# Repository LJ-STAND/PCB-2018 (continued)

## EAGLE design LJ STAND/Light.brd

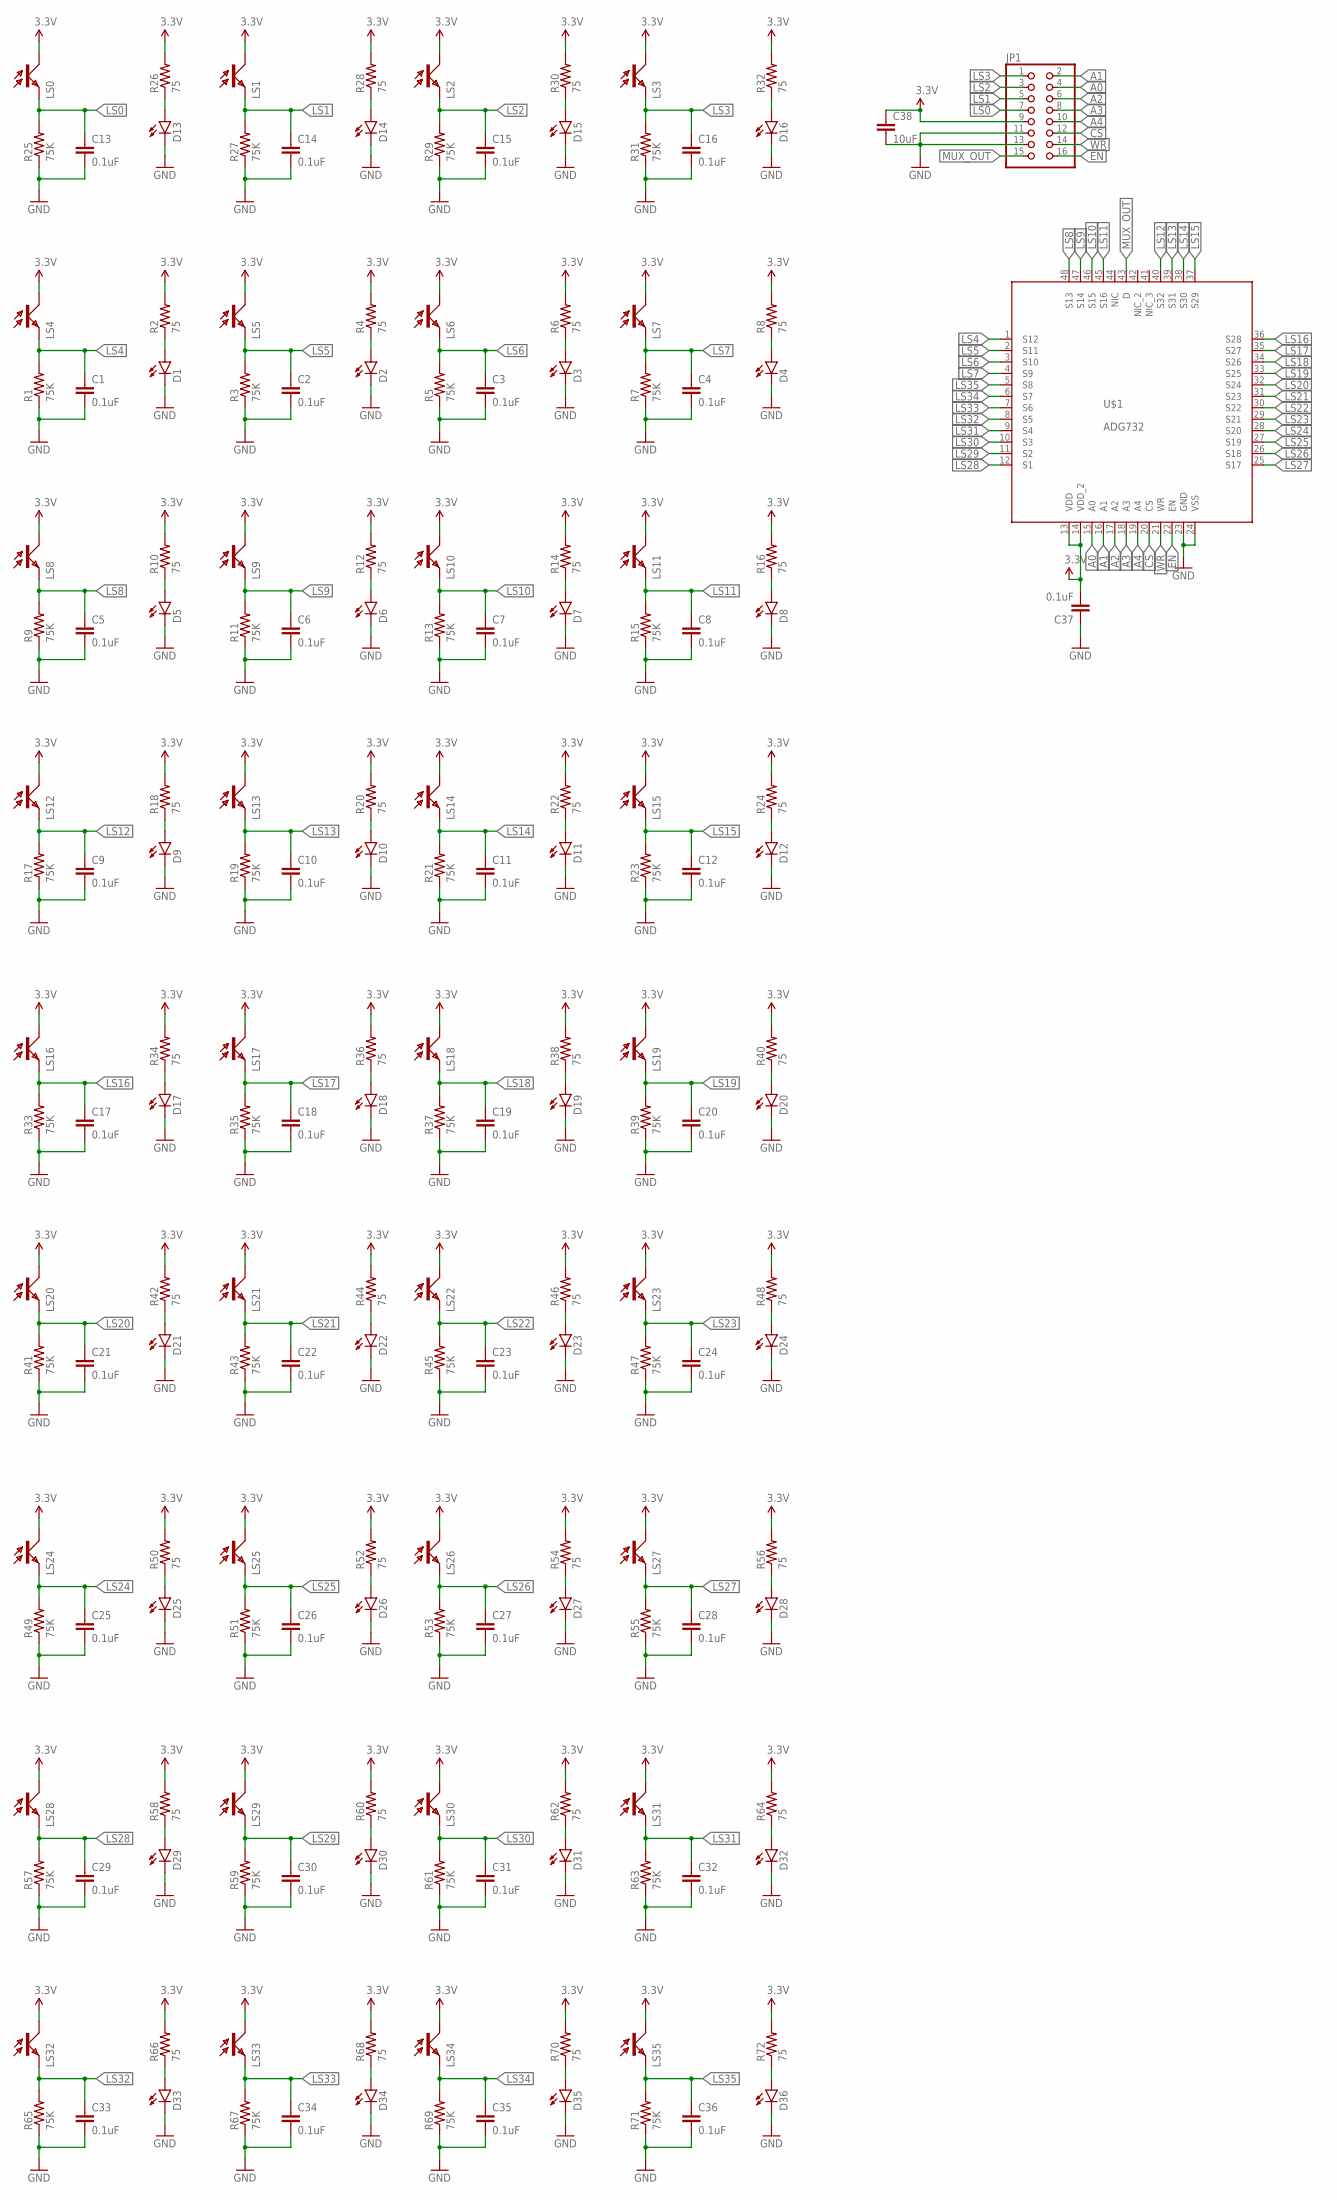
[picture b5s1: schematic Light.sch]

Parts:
C1, C2, C3, C4, C5, C6, C7, C8, C9, C10, C11, C12, C13, C14, C15, C16, C17, C18, C19, C20, C21, C22, C23, C24, C25, C26, C27, C28, C29, C30, C31, C32, C33, C34, C35, C36, C37: 0.1uF; 0603-CAP
C38: 10uF; 0805
D1, D2, D3, D4, D5, D6, D7, D8, D9, D10, D11, D12, D13, D14, D15, D16, D17, D18, D19, D20, D21, D22, D23, D24, D25, D26, D27, D28, D29, D30, D31, D32, D33, D34, D35, D36: LED0603; LED-0603
JP1: PINHD-2X8SMT; 2X08_SMT
LS0, LS1, LS2, LS3, LS4, LS5, LS6, LS7, LS8, LS9, LS10, LS11, LS12, LS13, LS14, LS15, LS16, LS17, LS18, LS19, LS20, LS21, LS22, LS23, LS24, LS25, LS26, LS27, LS28, LS29, LS30, LS31, LS32, LS33, LS34, LS35: ALS; SMD
R1, R3, R5, R7, R9, R11, R13, R15, R17, R19, R21, R23, R25, R27, R29, R31, R33, R35, R37, R39, R41, R43, R45, R47, R49, R51, R53, R55, R57, R59, R61, R63, R65, R67, R69, R71: 75K; 0603-RES
R2, R4, R6, R8, R10, R12, R14, R16, R18, R20, R22, R24, R26, R28, R30, R32, R34, R36, R38, R40, R42, R44, R46, R48, R50, R52, R54, R56, R58, R60, R62, R64, R66, R68, R70, R72: 75; 0603-RES
U$1: ADG732; QFP-7X7-48-NO-EXP

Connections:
3.3V: C37.2, C38.1, JP1.9, LS0.C, LS1.C, LS2.C, LS3.C, LS4.C, LS5.C, LS6.C, LS7.C, LS8.C, LS9.C, LS10.C, LS11.C, LS12.C, LS13.C, LS14.C, LS15.C, LS16.C, LS17.C, LS18.C, LS19.C, LS20.C, LS21.C, LS22.C, LS23.C, LS24.C, LS25.C, LS26.C, LS27.C, LS28.C, LS29.C, LS30.C, LS31.C, LS32.C, LS33.C, LS34.C, LS35.C, R2.2, R4.2, R6.2, R8.2, R10.2, R12.2, R14.2, R16.2, R18.2, R20.2, R22.2, R24.2, R26.2, R28.2, R30.2, R32.2, R34.2, R36.2, R38.2, R40.2, R42.2, R44.2, R46.2, R48.2, R50.2, R52.2, R54.2, R56.2, R58.2, R60.2, R62.2, R64.2, R66.2, R68.2, R70.2, R72.2, U$1.13 (VDD), U$1.14 (VDD_2)
A0: JP1.4, U$1.15 (A0)
A1: JP1.2, U$1.16 (A1)
A2: JP1.6, U$1.17 (A2)
A3: JP1.8, U$1.18 (A3)
A4: JP1.10, U$1.19 (A4)
CS: JP1.12, U$1.20 (CS)
EN: JP1.16, U$1.22 (EN)
GND: C1.2, C2.2, C3.2, C4.2, C5.2, C6.2, C7.2, C8.2, C9.2, C10.2, C11.2, C12.2, C13.2, C14.2, C15.2, C16.2, C17.2, C18.2, C19.2, C20.2, C21.2, C22.2, C23.2, C24.2, C25.2, C26.2, C27.2, C28.2, C29.2, C30.2, C31.2, C32.2, C33.2, C34.2, C35.2, C36.2, C37.1, C38.2, D1.C, D2.C, D3.C, D4.C, D5.C, D6.C, D7.C, D8.C, D9.C, D10.C, D11.C, D12.C, D13.C, D14.C, D15.C, D16.C, D17.C, D18.C, D19.C, D20.C, D21.C, D22.C, D23.C, D24.C, D25.C, D26.C, D27.C, D28.C, D29.C, D30.C, D31.C, D32.C, D33.C, D34.C, D35.C, D36.C, JP1.11, JP1.13, R1.1, R3.1, R5.1, R7.1, R9.1, R11.1, R13.1, R15.1, R17.1, R19.1, R21.1, R23.1, R25.1, R27.1, R29.1, R31.1, R33.1, R35.1, R37.1, R39.1, R41.1, R43.1, R45.1, R47.1, R49.1, R51.1, R53.1, R55.1, R57.1, R59.1, R61.1, R63.1, R65.1, R67.1, R69.1, R71.1, U$1.23 (GND), U$1.24 (VSS)
LS0: C13.1, JP1.7, LS0.E, R25.2
LS1: C14.1, JP1.5, LS1.E, R27.2
LS2: C15.1, JP1.3, LS2.E, R29.2
LS3: C16.1, JP1.1, LS3.E, R31.2
LS4: C1.1, LS4.E, R1.2, U$1.1 (S12)
LS5: C2.1, LS5.E, R3.2, U$1.2 (S11)
LS6: C3.1, LS6.E, R5.2, U$1.3 (S10)
LS7: C4.1, LS7.E, R7.2, U$1.4 (S9)
LS8: C5.1, LS8.E, R9.2, U$1.48 (S13)
LS9: C6.1, LS9.E, R11.2, U$1.47 (S14)
LS10: C7.1, LS10.E, R13.2, U$1.46 (S15)
LS11: C8.1, LS11.E, R15.2, U$1.45 (S16)
LS12: C9.1, LS12.E, R17.2, U$1.40 (S32)
LS13: C10.1, LS13.E, R19.2, U$1.39 (S31)
LS14: C11.1, LS14.E, R21.2, U$1.38 (S30)
LS15: C12.1, LS15.E, R23.2, U$1.37 (S29)
LS16: C17.1, LS16.E, R33.2, U$1.36 (S28)
LS17: C18.1, LS17.E, R35.2, U$1.35 (S27)
LS18: C19.1, LS18.E, R37.2, U$1.34 (S26)
LS19: C20.1, LS19.E, R39.2, U$1.33 (S25)
LS20: C21.1, LS20.E, R41.2, U$1.32 (S24)
LS21: C22.1, LS21.E, R43.2, U$1.31 (S23)
LS22: C23.1, LS22.E, R45.2, U$1.30 (S22)
LS23: C24.1, LS23.E, R47.2, U$1.29 (S21)
LS24: C25.1, LS24.E, R49.2, U$1.28 (S20)
LS25: C26.1, LS25.E, R51.2, U$1.27 (S19)
LS26: C27.1, LS26.E, R53.2, U$1.26 (S18)
LS27: C28.1, LS27.E, R55.2, U$1.25 (S17)
LS28: C29.1, LS28.E, R57.2, U$1.12 (S1)
LS29: C30.1, LS29.E, R59.2, U$1.11 (S2)
LS30: C31.1, LS30.E, R61.2, U$1.10 (S3)
LS31: C32.1, LS31.E, R63.2, U$1.9 (S4)
LS32: C33.1, LS32.E, R65.2, U$1.8 (S5)
LS33: C34.1, LS33.E, R67.2, U$1.7 (S6)
LS34: C35.1, LS34.E, R69.2, U$1.6 (S7)
LS35: C36.1, LS35.E, R71.2, U$1.5 (S8)
MUX_OUT: JP1.15, U$1.43 (D)
unnamed: D2.A, R4.1
unnamed: D1.A, R2.1
unnamed: D3.A, R6.1
unnamed: D4.A, R8.1
unnamed: D5.A, R10.1
unnamed: D6.A, R12.1
unnamed: D7.A, R14.1
unnamed: D8.A, R16.1
unnamed: D9.A, R18.1
unnamed: D10.A, R20.1
unnamed: D11.A, R22.1
unnamed: D12.A, R24.1
unnamed: D13.A, R26.1
unnamed: D14.A, R28.1
unnamed: D15.A, R30.1
unnamed: D16.A, R32.1
unnamed: D17.A, R34.1
unnamed: D18.A, R36.1
unnamed: D19.A, R38.1
unnamed: D20.A, R40.1
unnamed: D21.A, R42.1
unnamed: D22.A, R44.1
unnamed: D23.A, R46.1
unnamed: D24.A, R48.1
unnamed: D25.A, R50.1
unnamed: D26.A, R52.1
unnamed: D27.A, R54.1
unnamed: D28.A, R56.1
unnamed: D29.A, R58.1
unnamed: D30.A, R60.1
unnamed: D31.A, R62.1
unnamed: D32.A, R64.1
unnamed: D33.A, R66.1
unnamed: D34.A, R68.1
unnamed: D35.A, R70.1
unnamed: D36.A, R72.1
WR: JP1.14, U$1.21 (WR)

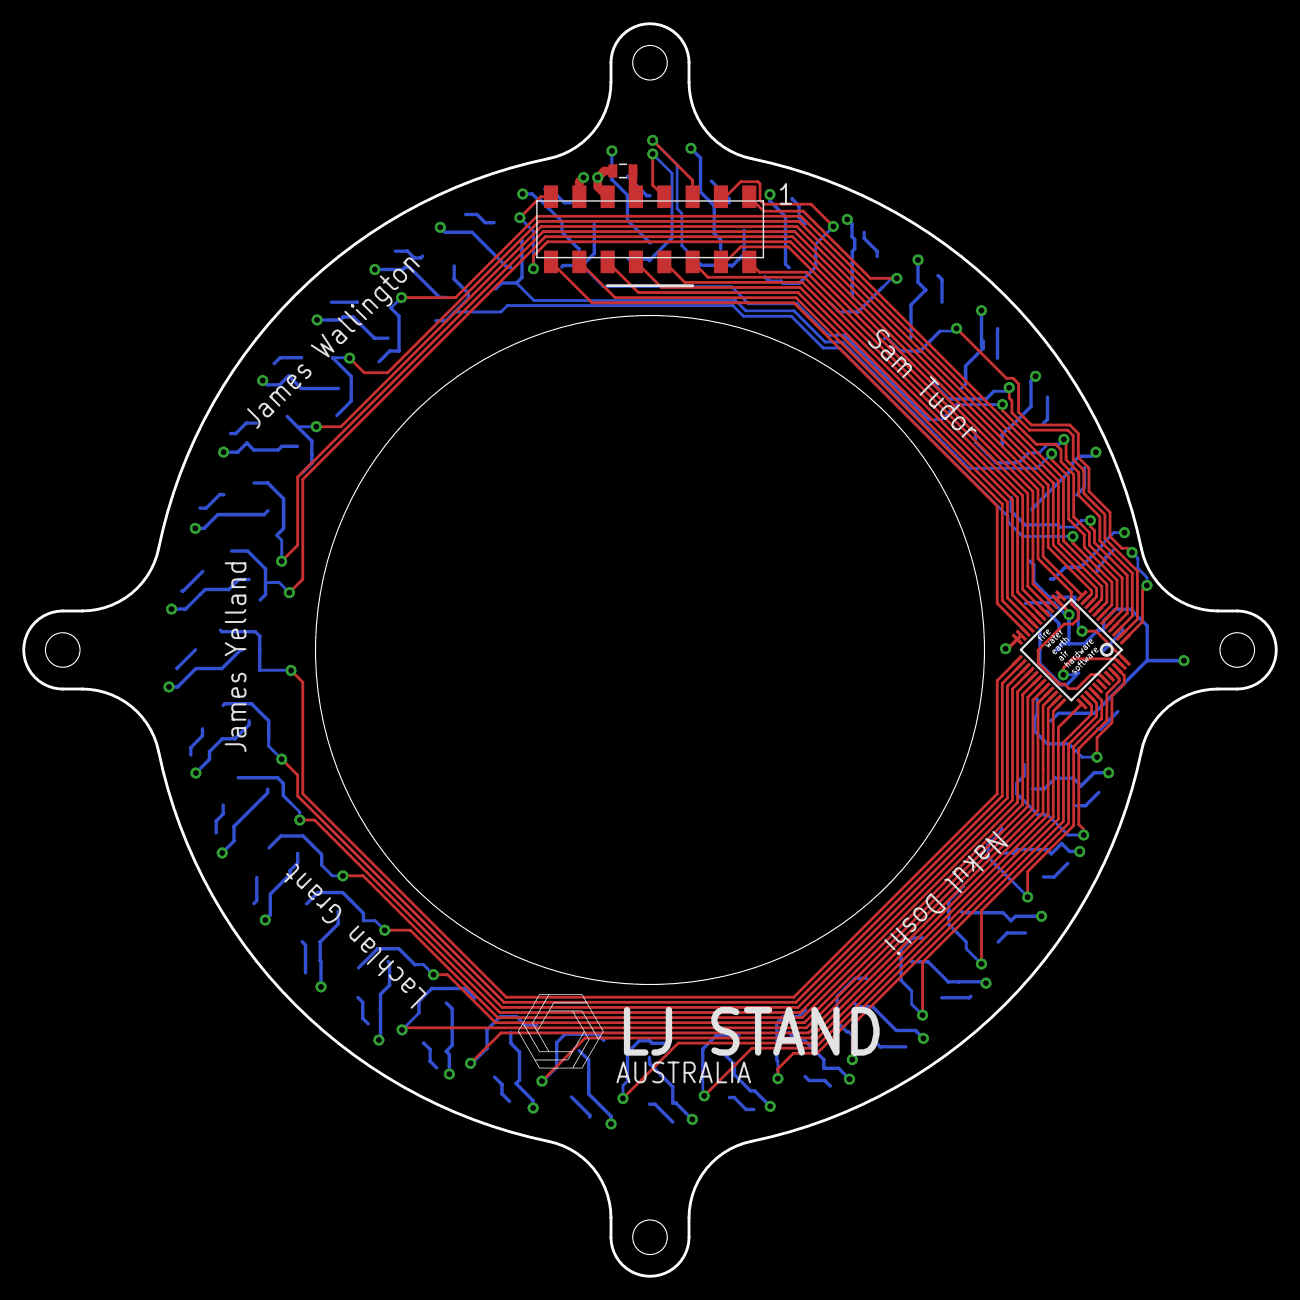
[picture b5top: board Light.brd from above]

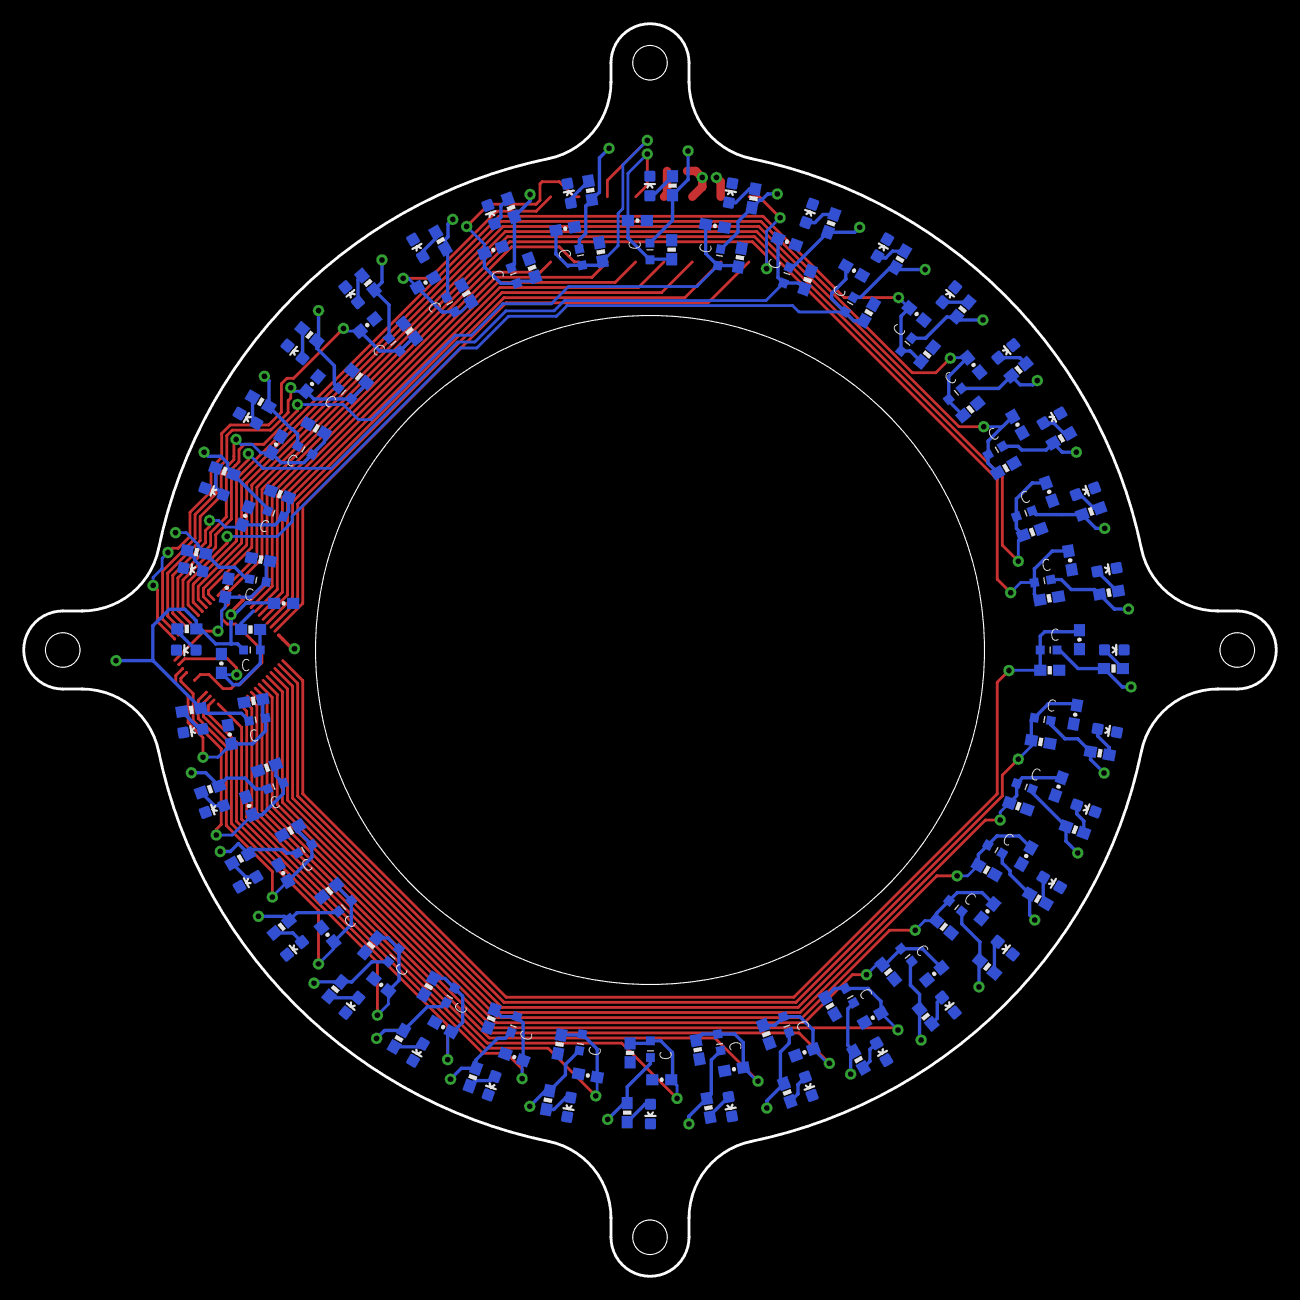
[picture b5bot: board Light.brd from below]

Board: 2 copper layers, 112.3 x 112.3 mm, 184 parts (181 on the bottom side), 83 nets.

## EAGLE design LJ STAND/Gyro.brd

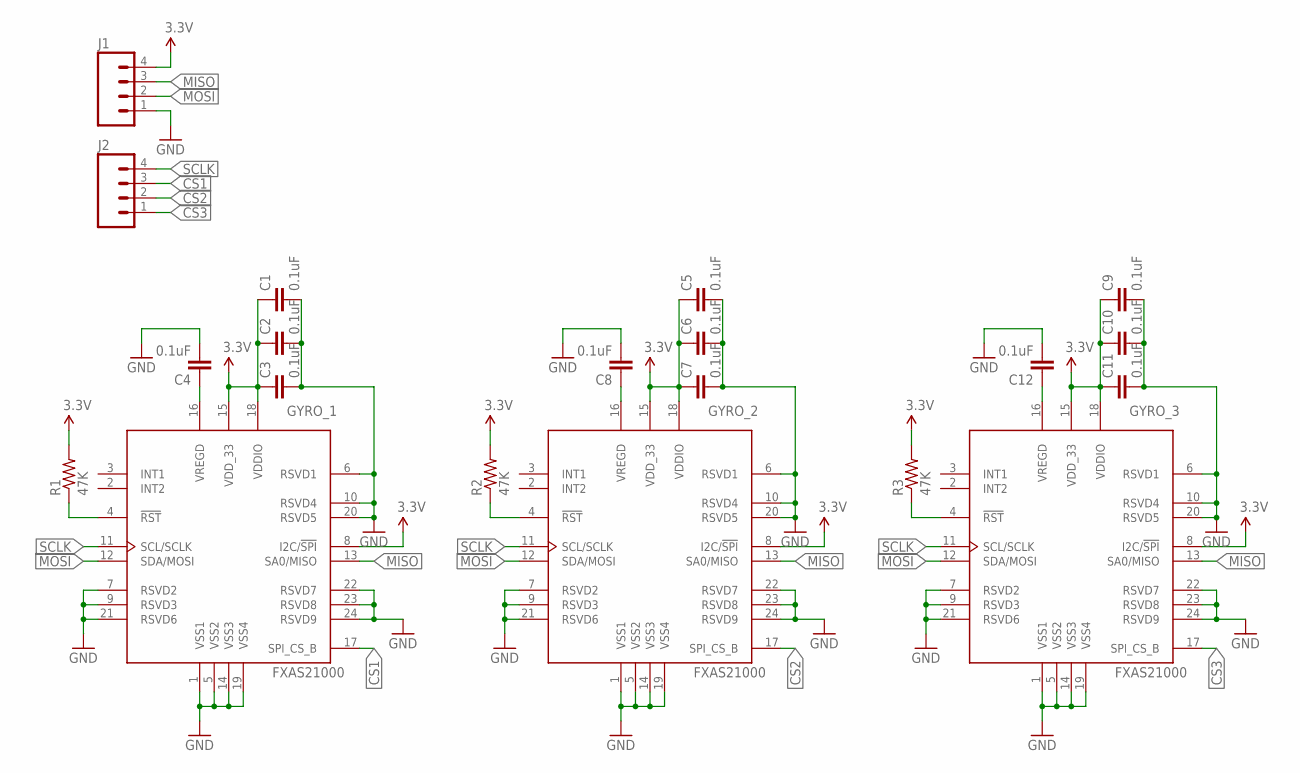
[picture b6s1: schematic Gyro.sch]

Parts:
C1, C2, C3, C4, C5, C6, C7, C8, C9, C10, C11, C12: 0.1uF; 0603-CAP
GYRO_1, GYRO_2, GYRO_3: FXAS21000; QFN24_0P5_4X4_ASYM_EXP
J1, J2: M04PTH; 1X04
R1, R2, R3: 47K; 0603-RES

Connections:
3.3V: C1.1, C2.1, C3.1, C5.1, C6.1, C7.1, C9.1, C10.1, C11.1, GYRO_1.8 (I2C/!SPI), GYRO_1.15 (VDD_33), GYRO_1.18 (VDDIO), GYRO_2.8 (I2C/!SPI), GYRO_2.15 (VDD_33), GYRO_2.18 (VDDIO), GYRO_3.8 (I2C/!SPI), GYRO_3.15 (VDD_33), GYRO_3.18 (VDDIO), J1.4, R1.2, R2.2, R3.2
CS1: GYRO_1.17 (SPI_CS_B), J2.3
CS2: GYRO_2.17 (SPI_CS_B), J2.2
CS3: GYRO_3.17 (SPI_CS_B), J2.1
GND: C1.2, C2.2, C3.2, C4.2, C5.2, C6.2, C7.2, C8.2, C9.2, C10.2, C11.2, C12.2, GYRO_1.1 (VSS1), GYRO_1.5 (VSS2), GYRO_1.6 (RSVD1), GYRO_1.7 (RSVD2), GYRO_1.9 (RSVD3), GYRO_1.10 (RSVD4), GYRO_1.14 (VSS3), GYRO_1.19 (VSS4), GYRO_1.20 (RSVD5), GYRO_1.21 (RSVD6), GYRO_1.22 (RSVD7), GYRO_1.23 (RSVD8), GYRO_1.24 (RSVD9), GYRO_2.1 (VSS1), GYRO_2.5 (VSS2), GYRO_2.6 (RSVD1), GYRO_2.7 (RSVD2), GYRO_2.9 (RSVD3), GYRO_2.10 (RSVD4), GYRO_2.14 (VSS3), GYRO_2.19 (VSS4), GYRO_2.20 (RSVD5), GYRO_2.21 (RSVD6), GYRO_2.22 (RSVD7), GYRO_2.23 (RSVD8), GYRO_2.24 (RSVD9), GYRO_3.1 (VSS1), GYRO_3.5 (VSS2), GYRO_3.6 (RSVD1), GYRO_3.7 (RSVD2), GYRO_3.9 (RSVD3), GYRO_3.10 (RSVD4), GYRO_3.14 (VSS3), GYRO_3.19 (VSS4), GYRO_3.20 (RSVD5), GYRO_3.21 (RSVD6), GYRO_3.22 (RSVD7), GYRO_3.23 (RSVD8), GYRO_3.24 (RSVD9), J1.1
MISO: GYRO_1.13 (SA0/MISO), GYRO_2.13 (SA0/MISO), GYRO_3.13 (SA0/MISO), J1.3
MOSI: GYRO_1.12 (SDA/MOSI), GYRO_2.12 (SDA/MOSI), GYRO_3.12 (SDA/MOSI), J1.2
unnamed: GYRO_1.4 (!RST), R1.1
unnamed: GYRO_2.4 (!RST), R2.1
unnamed: C8.1, GYRO_2.16 (VREGD)
unnamed: GYRO_3.4 (!RST), R3.1
unnamed: C12.1, GYRO_3.16 (VREGD)
unnamed: C4.1, GYRO_1.16 (VREGD)
SCLK: GYRO_1.11 (SCL/SCLK), GYRO_2.11 (SCL/SCLK), GYRO_3.11 (SCL/SCLK), J2.4

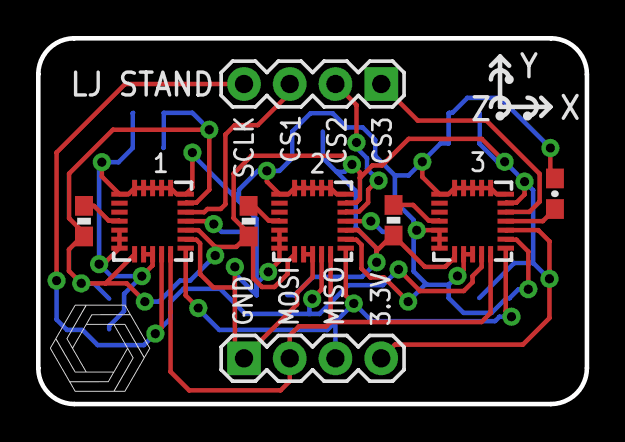
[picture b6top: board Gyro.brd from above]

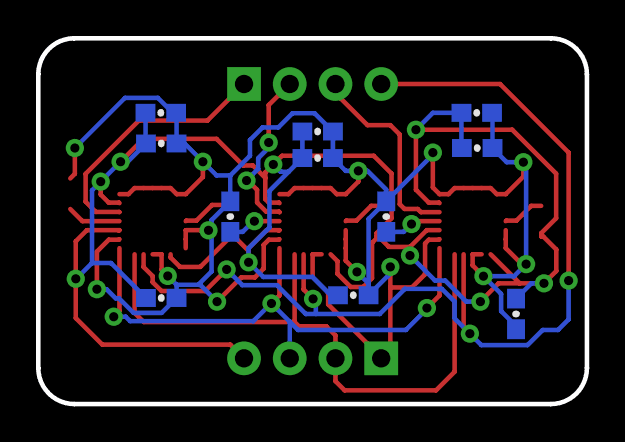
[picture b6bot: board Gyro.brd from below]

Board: 2 copper layers, 30.5 x 20.3 mm, 20 parts (11 on the bottom side), 14 nets.

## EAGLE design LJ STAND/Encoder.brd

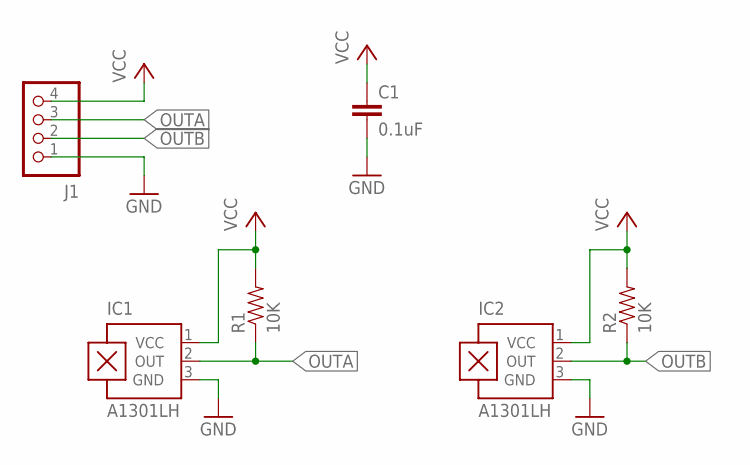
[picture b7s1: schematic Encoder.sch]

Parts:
C1: 0.1uF; 0603-CAP
IC1, IC2: A1301LH; SOT23-W
J1: B4B-PH-K-S
R1, R2: 10K; 0603-RES

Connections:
GND: C1.2, IC1.3 (GND), IC2.3 (GND), J1.1
OUTA: IC1.2 (OUT), J1.3, R1.1
OUTB: IC2.2 (OUT), J1.2, R2.1
VCC: C1.1, IC1.1 (VCC), IC2.1 (VCC), J1.4, R1.2, R2.2

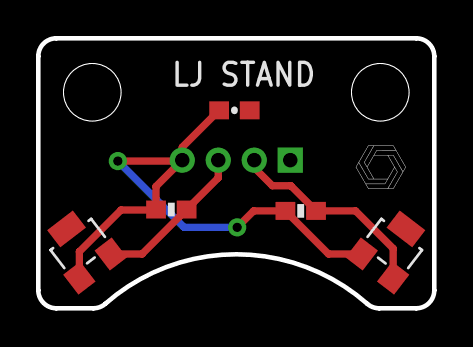
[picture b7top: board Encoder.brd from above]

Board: 2 copper layers, 22.0 x 15.0 mm, 6 parts (1 on the bottom side), 4 nets.

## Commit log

2018-02-21 Initial commit - added encoder PCB
2018-02-21 File saves
2018-02-21 gitignore
2018-02-21 Removed DS_Store
2018-02-28 Main & light schematics, preliminary board layout
2018-03-01 Light PCB routing
2018-03-05 Finished routing light & encoder pcbs
2018-03-06 Main PCB routing
2018-03-07 Finished routing main pcb
2018-03-07 Some small fixes to the main pcb
2018-03-07 Light gate plug labels
2018-03-08 Main edits, light gate pcbs
2018-03-10 Finalisation of gyro, encoder and light boards + gerbers, silkscreen fixes
2018-03-16 Pin changes on teensys, removed some screen pins for motor grounding
2018-03-17 Small fixes incl. grounding
2018-03-17 Final changes to main
2018-03-17 Final main + gerbers
2018-04-06 Gyro MPU9250 boards
2021-09-15 Removed backup files + README
